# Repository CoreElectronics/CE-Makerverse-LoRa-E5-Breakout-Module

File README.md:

# Makerverse™ LoRa-E5 Breakout

This is the repo for the [Makerverse™ LoRa-E5 Breakout](https://core-electronics.com.au/catalog/product/view/sku/CE09196).

## License
This project is open source - please review the LICENSE.md file for further licensing information.

If you have any technical questions, or concerns about licensing, please contact technical support on the [Core Electronics forums](https://forum.core-electronics.com.au/).

## Attribution
The hardware design of this module is influenced by the [Wio-E5 mini](https://wiki.seeedstudio.com/LoRa_E5_mini/).

*\"Makerverse\" and the Makerverse logo are trademarks of Core Electronics Pty Ltd.*

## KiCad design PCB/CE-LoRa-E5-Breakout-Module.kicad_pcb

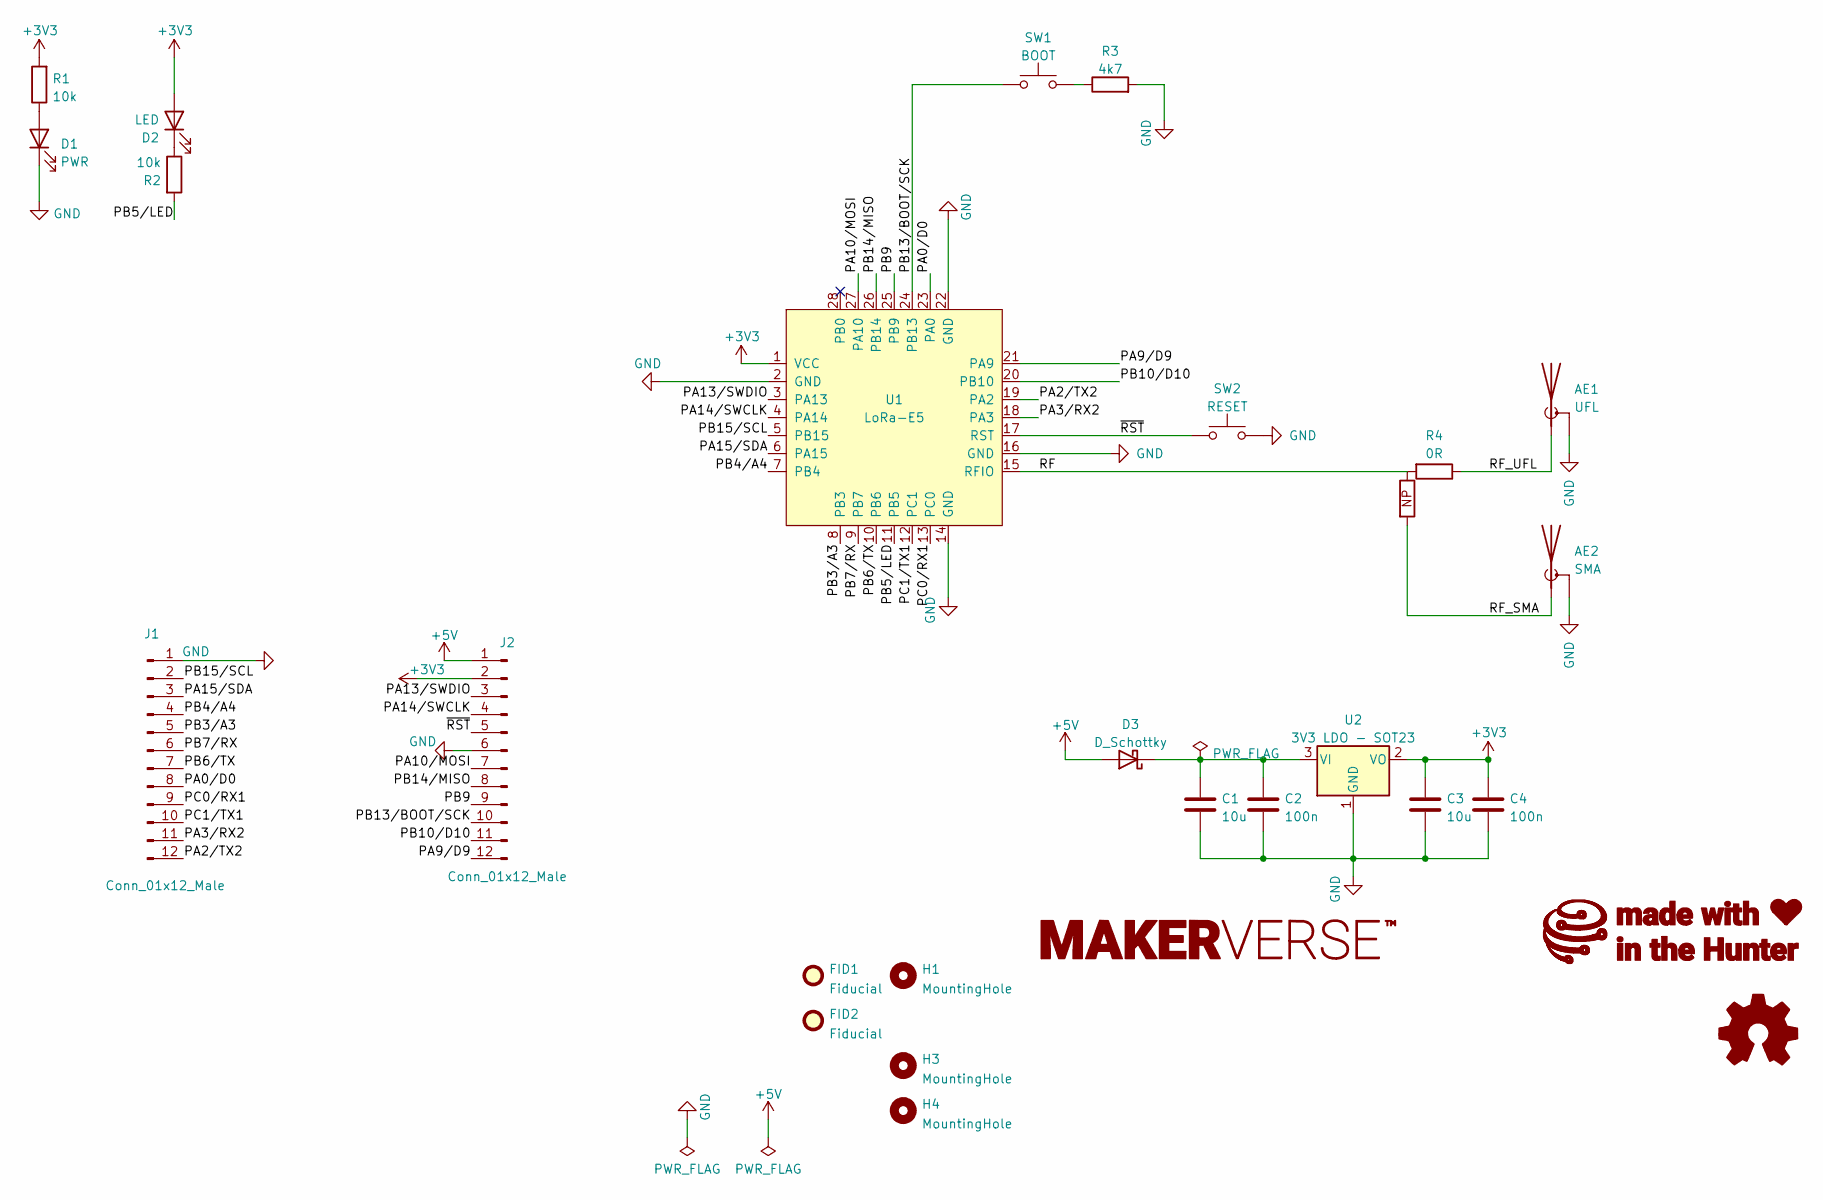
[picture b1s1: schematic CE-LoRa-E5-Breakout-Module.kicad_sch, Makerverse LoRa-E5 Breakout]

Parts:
AE1: UFL; U.FL_Hirose_U.FL-R-SMT-1_Vertical
AE2: SMA; Conn_RF_SMA_EdgeMount
C1, C3: 10u; C_0603_1608Metric
C2, C4: 100n; C_0402_1005Metric
D1: PWR; LED_0603_1608Metric
D2: LED; LED_0603_1608Metric
D3: D_Schottky; D_SMA
FID1, FID2: Fiducial; Fiducial_1mm_Mask2mm
G1: LOGO_Makerverse; makerverse_logo_short_14.0x2.4mm
G2: LOGO_CoreElectronics_made-with-love; makerverse_logo_35.8x4.2mm
H1, H3, H4: MountingHole; MountingHole_3.2mm_M3
J1, J2: Conn_01x12_Male; PinHeader_1x12_P2.54mm_Vertical
LOGO1: Logo_Open_Hardware_Small; oshw_3.9x3.5mm
R1, R2: 10k; R_0402_1005Metric
R3: 4k7; R_0402_1005Metric
R4: 0R; Jumper_Resistor_SPDT_0603_1608Metric
SW1: BOOT; SW_SPST_TL3342
SW2: RESET; SW_SPST_TL3342
U1: LoRa-E5
U2: 3V3 LDO - SOT23; SOT-23

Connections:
+3V3: C3.1, C4.1, D2.2 (A), J2.2, R1.2, U1.1 (VCC), U2.2 (VO)
+5V: D3.2 (A), J2.1
/PA0/D0: J1.8, U1.23 (PA0)
/PA2/TX2: J1.12, U1.19 (PA2)
/PA3/RX2: J1.11, U1.18 (PA3)
/PA9/D9: J2.12, U1.21 (PA9)
/PA10/MOSI: J2.7, U1.27 (PA10)
/PA13/SWDIO: J2.3, U1.3 (PA13)
/PA14/SWCLK: J2.4, U1.4 (PA14)
/PA15/SDA: J1.3, U1.6 (PA15)
/PB3/A3: J1.5, U1.8 (PB3)
/PB4/A4: J1.4, U1.7 (PB4)
/PB5/LED: R2.2, U1.11 (PB5)
/PB6/TX: J1.7, U1.10 (PB6)
/PB7/RX: J1.6, U1.9 (PB7)
/PB9: J2.9, U1.25 (PB9)
/PB10/D10: J2.11, U1.20 (PB10)
/PB13/BOOT/SCK: J2.10, SW1.1, U1.24 (PB13~)
/PB14/MISO: J2.8, U1.26 (PB14)
/PB15/SCL: J1.2, U1.5 (PB15)
/PC0/RX1: J1.9, U1.13 (PC0)
/PC1/TX1: J1.10, U1.12 (PC1)
/RF: R4.2, U1.15 (RFIO)
/RF_SMA: AE2.1 (A), R4.3
/RF_UFL: AE1.1 (A), R4.1
/~RST: J2.5, SW2.1, U1.17 (RST)
GND: AE1.2 (Shield), AE2.2 (Shield), C1.2, C2.2, C3.2, C4.2, D1.1 (K), J1.1, J2.6, R3.2, SW2.2, U1.2 (GND), U1.14 (GND), U1.16 (GND), U1.22 (GND), U2.1 (GND)
unnamed: C1.1, C2.1, D3.1 (K), U2.3 (VI)
unnamed: D1.2 (A), R1.1
unnamed: D2.1 (K), R2.1
unnamed: R3.1, SW1.2

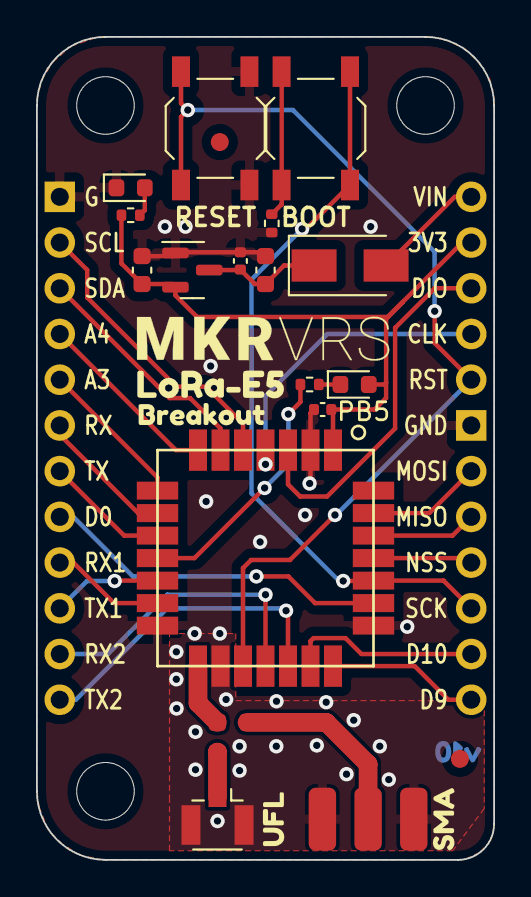
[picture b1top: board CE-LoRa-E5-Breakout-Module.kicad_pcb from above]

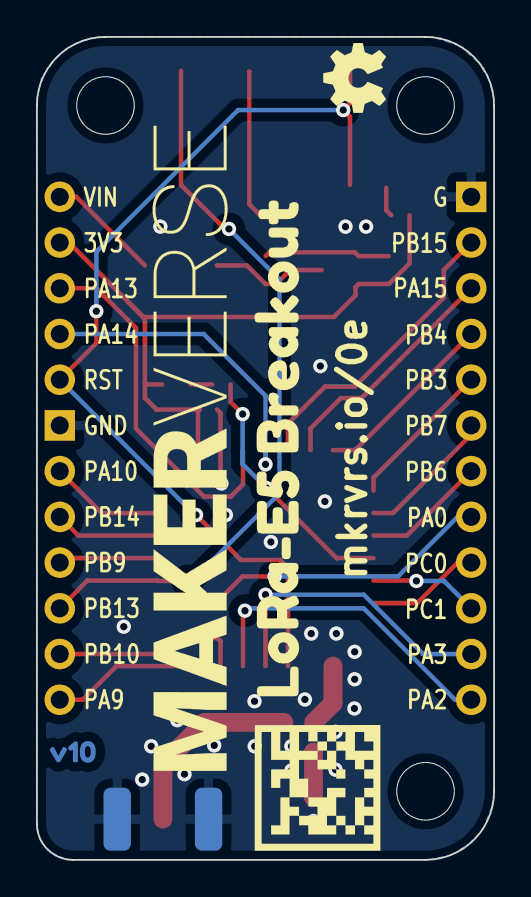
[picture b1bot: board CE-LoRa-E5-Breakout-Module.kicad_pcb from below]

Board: 2 copper layers, 25.4 x 45.7 mm, 33 parts (6 on the bottom side), 31 nets.

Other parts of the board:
kibuzzard-63AE194F: G***; kibuzzard-63AE194F
kibuzzard-635A0587: G***; kibuzzard-635A0587
kibuzzard-635B4E71: G***; kibuzzard-635B4E71
kibuzzard-635B4E81: G***; kibuzzard-635B4E81
kibuzzard-639FDA33: G***; kibuzzard-639FDA33
kibuzzard-639FDA51: G***; kibuzzard-639FDA51

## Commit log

2022-10-28 v0 initial commit
2022-12-19 v02 prototype with SMA connector option

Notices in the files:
PCB/CE-LoRa-E5-Breakout-Module.kicad_sch:
https://creativecommons.org/licenses/by-sa/4.0
Released under CC BY SA 4.0
